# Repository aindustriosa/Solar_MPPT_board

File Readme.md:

# Propósito
Con este proxecto pretendemos crear unha pequena plataforma educacional de xestión de enerxía solar baseada no Hardware e Software empregado por un dos equipos da Industriosa participante nas edicións 2018 e 2019 da Regata Solar de Marine Instruments coa que obtivemos a victoria en ambas edicións na categoría Open.

https://www.regatasolar.org/

A idea é que o sistema sexa o suficientemente sinxelo de montar e integrar que poida ser usado polos equipos de estudantes.

# Técnica

A complexidade de construir un vehículo solar sen acumulación de enerxía radica en conseguir exprimir ó máximo as posibilidades do panel solar.
Os paneles entregan enerxía eléctrica seguindo unha curva característica que fai necesaria unha xestión intelixente da demanda do sistema de propulsión. É necesario atopar o punto de máxima potencia: se demandamos menos do que o panel é capaz de entregar, desaproveitamos enerxía, e se demandamos máis do que é capaz de entregar, o panel vense abaixo e a potencia entregada cae dramáticamente ata provocar un apagado do sistema.

A continuación unha curva característica de entrega de potencia dun panel solar:

A estratexia seguida para conseguir o propósito consiste en monitorizar constantemente a corrente e tensión entregadas polo panel (e, por tanto, a potencia) e modular mediante un algoritmo software a demanda do motor de propulsión para conseguir en todo momento a máxima potencia disponible.
Este algoritmo ten que ser capaz de auto-adaptarse para facer fronte ás cambiantes condicións nas que o panel se atopa:
* Cambios na radiación solar
* Modificación na posición do panel con respecto do sol
* Cambios na resistencia do motor segundo as condicións dinámicas da embarcación
* ...

# Hardware

A PCB conta con tódolos seus componentes en montaxe Through Hole (Furado pasante) e módulos insertables:
* Arduino Nano
* INA219
* Bluetooth HC-05

E conexións cos diferentes elementos que compoñen toda a electróncia do barco solar:
* Entrada de panel solar
* Saída de alimentación para o ESC
* Entrada de batería (receptor R/C)
* 4x Entradas PWM de sináis provintes do receptor de R/C
* 4x Saídas PWM para ESC, Servos, ...
* Conexión módulo Bluetooth HC05

Esquema básico de montaxe:

Os jumpers JP1 e JP2 sirven para conectar os rails de 5V e/ou Vin cos pines de alimentación das entradas e saídas PPM.
Nesta montaxe, se queremos alimentar todo o sistema a través do BEC do ESC conectaremos JP2 con Vin (caso de BEC de 6V) ou con +5V (caso de BEC de 5V). Para alimentar o receptor de radio, conectaremos JP1 para que no pin de alimentación das entradas esté disponible +5V ou Vin, según se desexe.

Na wiki do proxecto detállase o pinout dos diferentes conectores. Recoméndase revisar o esquemático para ter completamente claro o uso de estos jumpers.

https://github.com/aindustriosa/Solar_MPPT_board/wiki

### NOTA: A PCB do INA219 debe ser modificada para poder medir corrente no rango que entrega o panel. Recoméndase sustituir a resisntencia de Shunt orixinal de 0R1 por unha de 0R025.

# Software

A peza principal do código é unha implementación do algoritmo MPPT "Perturb and Observe".
Sirva como guía para comprender a implementación o seguinte documento:

http://ww1.microchip.com/downloads/en/appnotes/00001521a.pdf

En esencia, o algoritmo adapta a demanda que se fai do motor do seguinte modo:
1. Mide Corrente entregada polo panel
2. Mide a Tensión á saída do panel
3. Calcula a potencia
4. Compara coa potencia na anterior iteración
5. Incrementa ou decrementa PWM (ver grafo)

# Licenza

## Hardware

Diseñado por Luis Miranda e Hernán Serrano baixo licenza CERN OPEN HARDWARE LICENCE v1.2 http://www.ohwr.org/
Esta licenza aplica ós deseños Hardware e documentación contida na carpeta 'MPPT PCB' de este repositorio.

Designed by Luis Miranda & Hernán Serrano under CERN OPEN HARDWARE LICENCE v1.2 http://www.ohwr.org/
This license applies to hardware designs and documentation which reside in the 'MPPT PCB' folder of this repository.

## Software

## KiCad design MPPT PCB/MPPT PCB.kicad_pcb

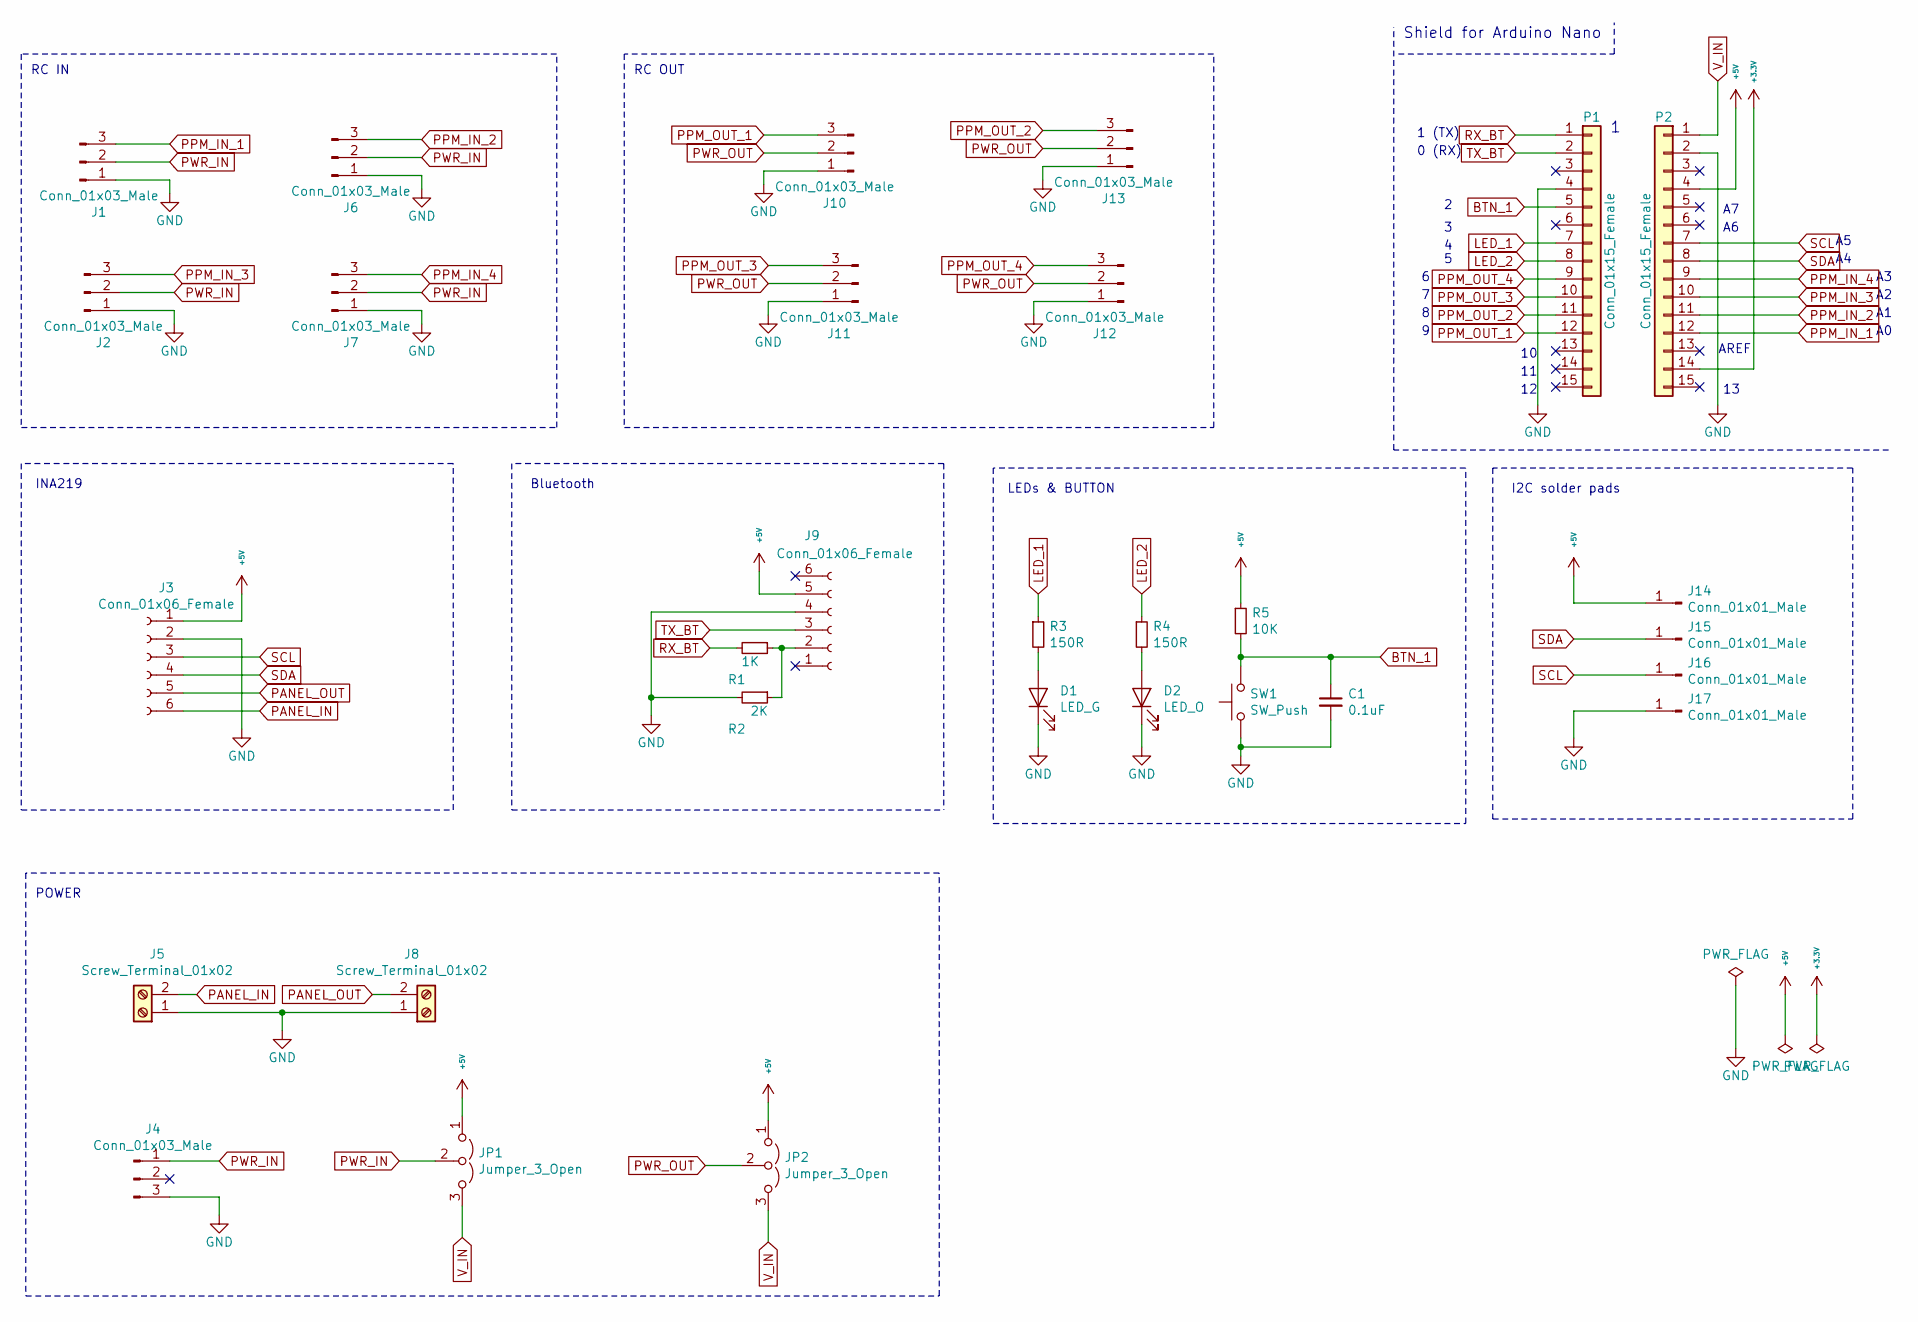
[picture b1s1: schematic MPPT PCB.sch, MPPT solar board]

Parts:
C1: 0.1uF; C_Disc_D3.0mm_W1.6mm_P2.50mm; DIGIKEY_PN 478-3192-ND
D1: LED_G; LED_D3.0mm; DIGIKEY_PN 732-5008-ND
D2: LED_O; LED_D3.0mm; DIGIKEY_PN 732-5010-ND
J1, J2, J4, J6, J7, J10, J11, J12, J13: Conn_01x03_Male; PinHeader_1x03_P2.54mm_Vertical; DIGIKEY_PN 732-5316-ND
J3, J9: Conn_01x06_Female; PinSocket_1x06_P2.54mm_Vertical; DIGIKEY_PN SAM1213-06-ND
J5, J8: Screw_Terminal_01x02; TerminalBlock_bornier-2_P5.08mm; DIGIKEY_PN A98076-ND
J14, J15, J16, J17: Conn_01x01_Male; Test_Point_2.67x1.02mm
JP1, JP2: Jumper_3_Open; PinHeader_1x03_P2.54mm_Vertical; DIGIKEY_PN 732-5316-ND
P1, P2: Conn_01x15_Female; Socket_Strip_Arduino_1x15; DIGIKEY_PN SAM1213-15-ND
R1: 1K; R_Axial_DIN0207_L6.3mm_D2.5mm_P10.16mm_Horizontal; DIGIKEY_PN CF14JT1K00CT-ND
R2: 2K; R_Axial_DIN0207_L6.3mm_D2.5mm_P10.16mm_Horizontal; DIGIKEY_PN CF14JT2K00CT-ND
R3, R4: 150R; R_Axial_DIN0207_L6.3mm_D2.5mm_P10.16mm_Horizontal; DIGIKEY_PN CF14JT150RCT-ND
R5: 10K; R_Axial_DIN0207_L6.3mm_D2.5mm_P10.16mm_Horizontal; DIGIKEY_PN CF14JT10K0CT-ND
SW1: SW_Push; SW_Tactile_Straight_KSA0Axx1LFTR; DIGIKEY_PN CKN12261-ND

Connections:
+3V3: P2.14
+5V: J3.1, J9.5, J14.1, JP1.1 (A), JP2.1 (A), P2.4, R5.1
BTN_1: C1.1, P1.5, R5.2, SW1.2
GND: C1.2, D1.1 (K), D2.1 (K), J1.1, J2.1, J3.2, J4.3, J5.1, J6.1, J7.1, J8.1, J9.4, J10.1, J11.1, J12.1, J13.1, J17.1, P1.4, P2.2, R2.2, SW1.1
LED_1: P1.7, R3.1
LED_2: P1.8, R4.1
unnamed: D1.2 (A), R3.2
unnamed: D2.2 (A), R4.2
unnamed: J9.2, R1.1, R2.1
PANEL_IN: J3.6, J5.2
PANEL_OUT: J3.5, J8.2
PPM_IN_1: J1.3, P2.12
PPM_IN_2: J6.3, P2.11
PPM_IN_3: J2.3, P2.10
PPM_IN_4: J7.3, P2.9
PPM_OUT_1: J10.3, P1.12
PPM_OUT_2: J13.3, P1.11
PPM_OUT_3: J11.3, P1.10
PPM_OUT_4: J12.3, P1.9
PWR_IN: J1.2, J2.2, J4.1, J6.2, J7.2, JP1.2 (C)
PWR_OUT: J10.2, J11.2, J12.2, J13.2, JP2.2 (C)
RX_BT: P1.1, R1.2
SCL: J3.3, J16.1, P2.7
SDA: J3.4, J15.1, P2.8
TX_BT: J9.3, P1.2
V_IN: JP1.3 (B), JP2.3 (B), P2.1

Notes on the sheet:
Shield for Arduino Nano
1 (TX)
0 (RX)
AREF
RC IN
RC OUT
INA219
Bluetooth
POWER
LEDs & BUTTON
I2C solder pads

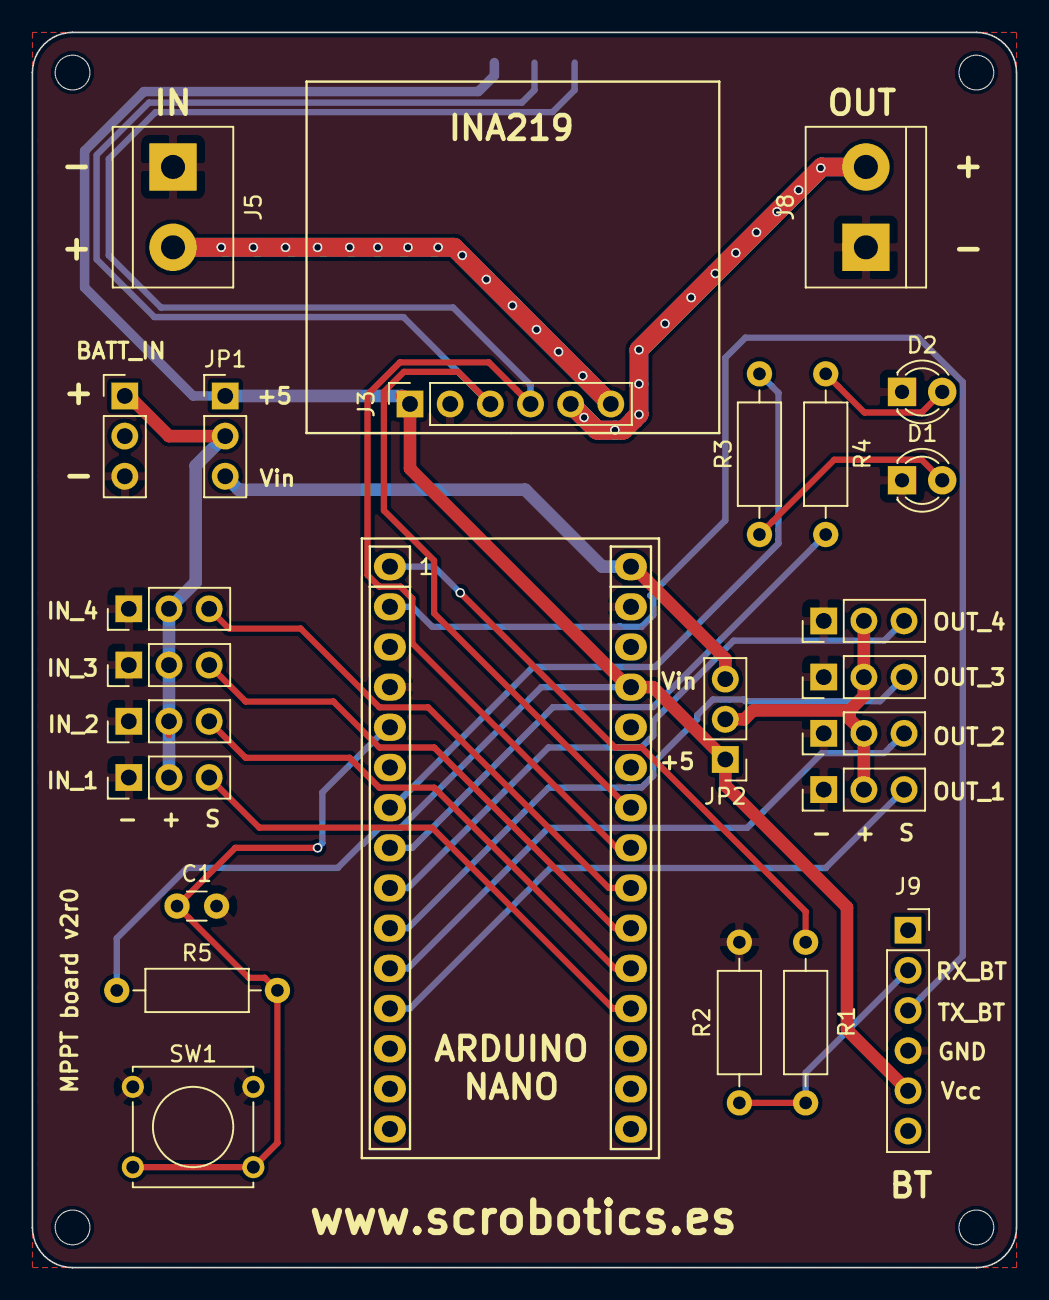
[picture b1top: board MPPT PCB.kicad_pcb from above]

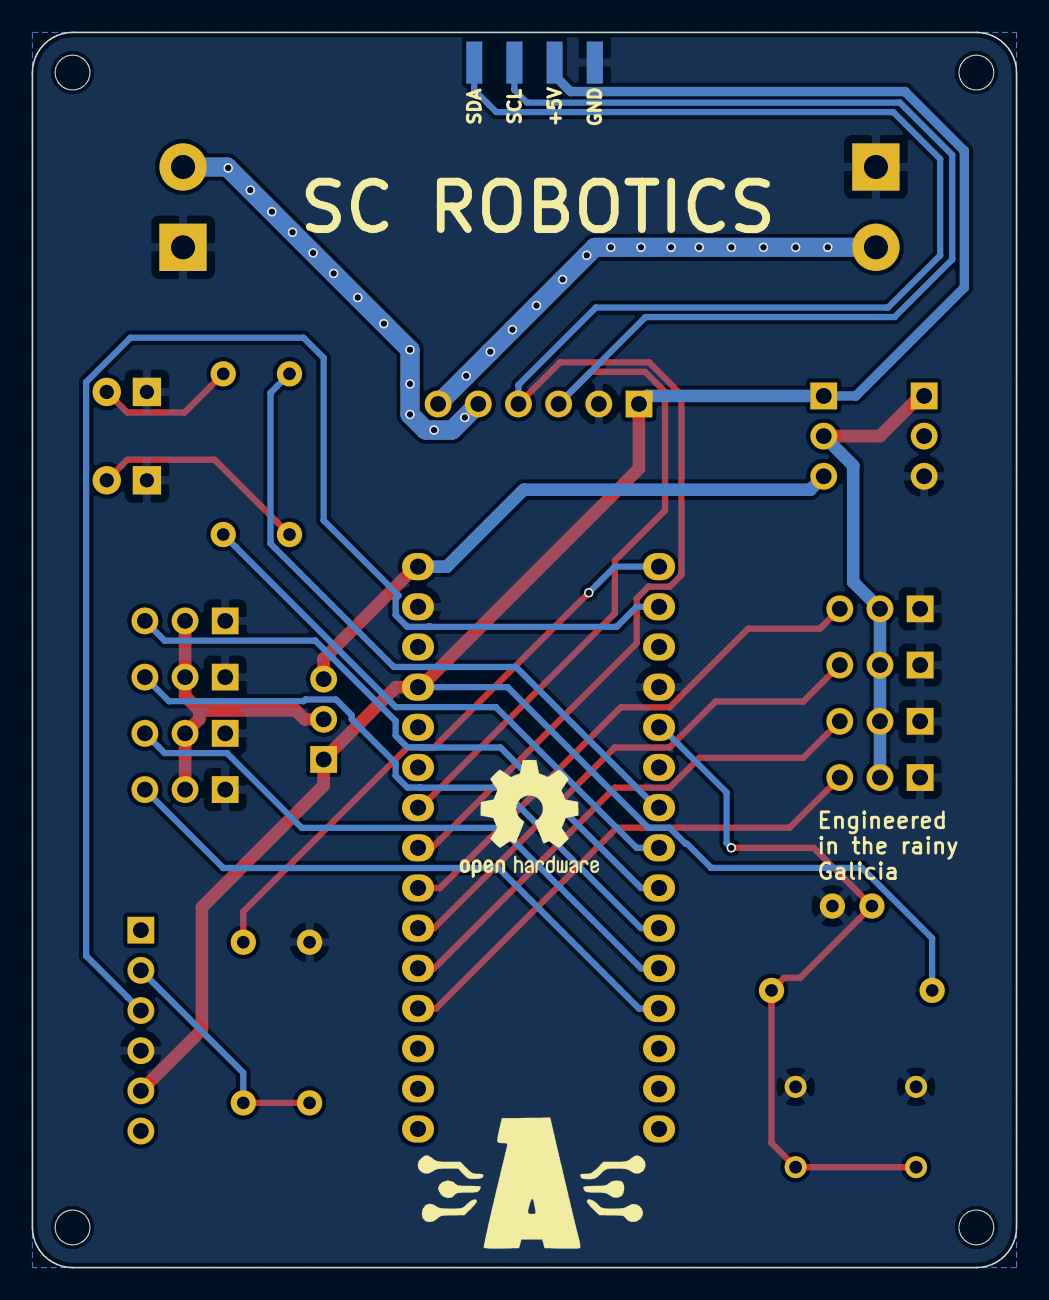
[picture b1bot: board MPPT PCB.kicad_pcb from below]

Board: 2 copper layers, 62.2 x 78.1 mm, 30 parts (4 on the bottom side), 25 nets.

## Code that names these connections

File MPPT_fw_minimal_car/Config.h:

// Definición de pines de Arduino Nano
#define LED1 4
#define LED2 5
#define BTN 2
#define PPM_OUT_1 9
#define PPM_OUT_2 8
#define PPM_OUT_3 7
#define PPM_OUT_4 6
#define PPM_IN_1 A0
#define PPM_IN_2 A1
#define PPM_IN_3 A2
#define PPM_IN_4 A3

// Parámetros de configuración xerais
#define CICLE_TIMER 100   //tempo de ciclo en ms
#define CICLE_SAMPLES 10  //mostras por ciclo
#define PPM_DECREMENTO 3   //cantidade decrementada en caso de limitar
#define PPM_INCREMENTO 2  //aceleración
#define UMBRAL_VOLT 12    //voltaxe por debaixo da cal se limita
#define REV_SPEED 40    //velocidad fija en reversa

// Estados FSM
#define AVANCE 0
#define LIMITADO 1
#define REVERSA 2

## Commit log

2019-10-08 PCB proto version
2019-10-08 Added AI logo files
2019-10-12 Minor changes. Added images.
2019-10-12 Changed render file name
2019-10-12 Added image
2019-10-12 Changed image size
2019-10-12 Fixed servo pinout (Input and Output)
2019-11-05 Firmware sin refactorizar
2019-11-05 Readme
2020-01-16 Version 2 of PCB
2020-01-16 Changed front PCB render
2020-01-16 Included algorithm graph
2020-01-16 typpo
2020-01-20 Deleted html from gitignore
2020-01-20 Added PCB BOM
2020-01-20 Added Hardware License terms
2020-01-31 Added basic hardware scheme
2020-01-31 Image changes
2020-01-31 Image size changed
2020-01-31 Added jumper description
2020-01-31 Fixed image routes
2020-02-17 Add minimal car firmware for MPPT board
2020-02-17 Add pinout image
2020-02-17 Add link to wiki
2020-02-18 Fix LED output pin configuration and colour
2020-02-19 INA219 information
2020-04-08 Add gerber files
